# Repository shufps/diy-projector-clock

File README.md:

# DIY Night Projector Clock

A Clock Projector can project the time to a ceiling in the night.

There are lots of commercial alarm clocks with integrated clock projector on the market but I thought, it would be fun to build one myself.

Moreover it was a good project for becoming accustomed to the process of 3d-designing cases which can be 3d printed and to learn about designing tolerances.

The principle is easy – basically it works like a video beamer (or any other projecting clock^^).

## LCD and Calculations
I choosed a small negative (background black) 64×32 LCD which has the dimensions of just 15mm x 12mm (active area 11.18mm x 5.58mm).

The goal was to build a complete projector with not more than 50mm x 50mm x 50mm (which I didn’t managed … But close to^^).

A small LCD has the advantage that everything becomes smaller and cheaper – this influences heavily costs for optics because a smaller LCD needs smaller optics to project an low distorted image.

Moreover a smaller LCD needs smaller focal length for a decent sized imaged on the ceiling. A good distance would be 2m from LCD to ceiling.

The formula for image width depending from the focal length is defined as:

with:
– S2 distance from lens to LCD and
– S1 distance from lens to ceiling
– W2 is the width of the LCD
– W1 is the width of the projected image

The formulas show that the smaller the focal length the larger the projected image will be.

I decided to go for 25mm because there are cheap lenses which can be obtained for about $12 in china.

For our values that would magnify the image by about x80 – 11.1mm LCD width would become 88.1cm image width on the ceiling in a distance of 2m.

## Light and Condensor Lens
It was not really clear how strong a LED has to be in order to get a reasonable well readable picture in the night on the ceiling.

To be sure – actually I wasn’t really – I decided to use a high power LED with 1W and use a cheap chinese condensor lense to parallelize the light before it passes the LCD (this has do be done anyway but a condensor lens makes it possible to use more light because condensors are shaped in a way that allowes to get the lens as near to the LED as possible – so catching more light).

The two pictures show the condensor-lense which is directly mounted to the PCB the resulting light spot on the ceiling. It is a really gread lens which is made for my LED – so it fits perfectly and parallelizes the light nicely.

## Electronics Construction
Two PCBs were designed – one holding the LCD and the actual projecting board.

The latter is equipped with 1W LED driver, STM32F103 Cortex ARM, a rotary encoder (for changing settings like brightness, standby-timer, time, …), USB, IR (both not used yet).

## Mechanics Construction
Originally, I aimed for 50mm x 50mm x 50mm but I only managed to get to 60mm x 60mm x 60mm 😥 😉

Here an overview about all I designed:

From left to right: Case with DIY projection lens (I skip this part – it worked but not really well), Sony E-Mount, C-Mount. In the middle the rest.

## LCD-Holder
A custom LCD-holder was designed to perfectly mount the LCD on the right place on the PCB.

## Case – C-Mount Variant
There are incredibly cheap chinase C-Mount lenses with a focal length of 25mm. They are sooo cheap that image quality is really really bad when using for fotography.

But surprisingly it works (almost) perfect for the Mini DIY Projector 😀

The pillow-effect (optical distortion where the edges are not straight but bent outwards) is almost neglectable – resulting a much better image than I expected (after reading reviews to this lense)

## Case – Sony E-Mount Variant
Just for fun – and because I have a 3d printer which works reliably without much attention – I did a variant for Sony E-Mount.

Here the projector with Walimex Pro 10mm 2.8 lens.

I have to admit – it isn’t that bright in reality but it’s still very readable although it is so large.

The image has more than 2m in width! And distortions almost non-existent 🙂

Downloads
GitHub-Repository contains:
– Schematic
– Layout
– Bill of material
– STM32 Cortex ARM Source
– 3D-STL-Files
– Images

Thingiverse: https://www.thingiverse.com/thing:2887852

Archive of original site: https://web.archive.org/web/20241128173803/https://microengineer.eu/2018/05/01/diy-night-clock-projector/

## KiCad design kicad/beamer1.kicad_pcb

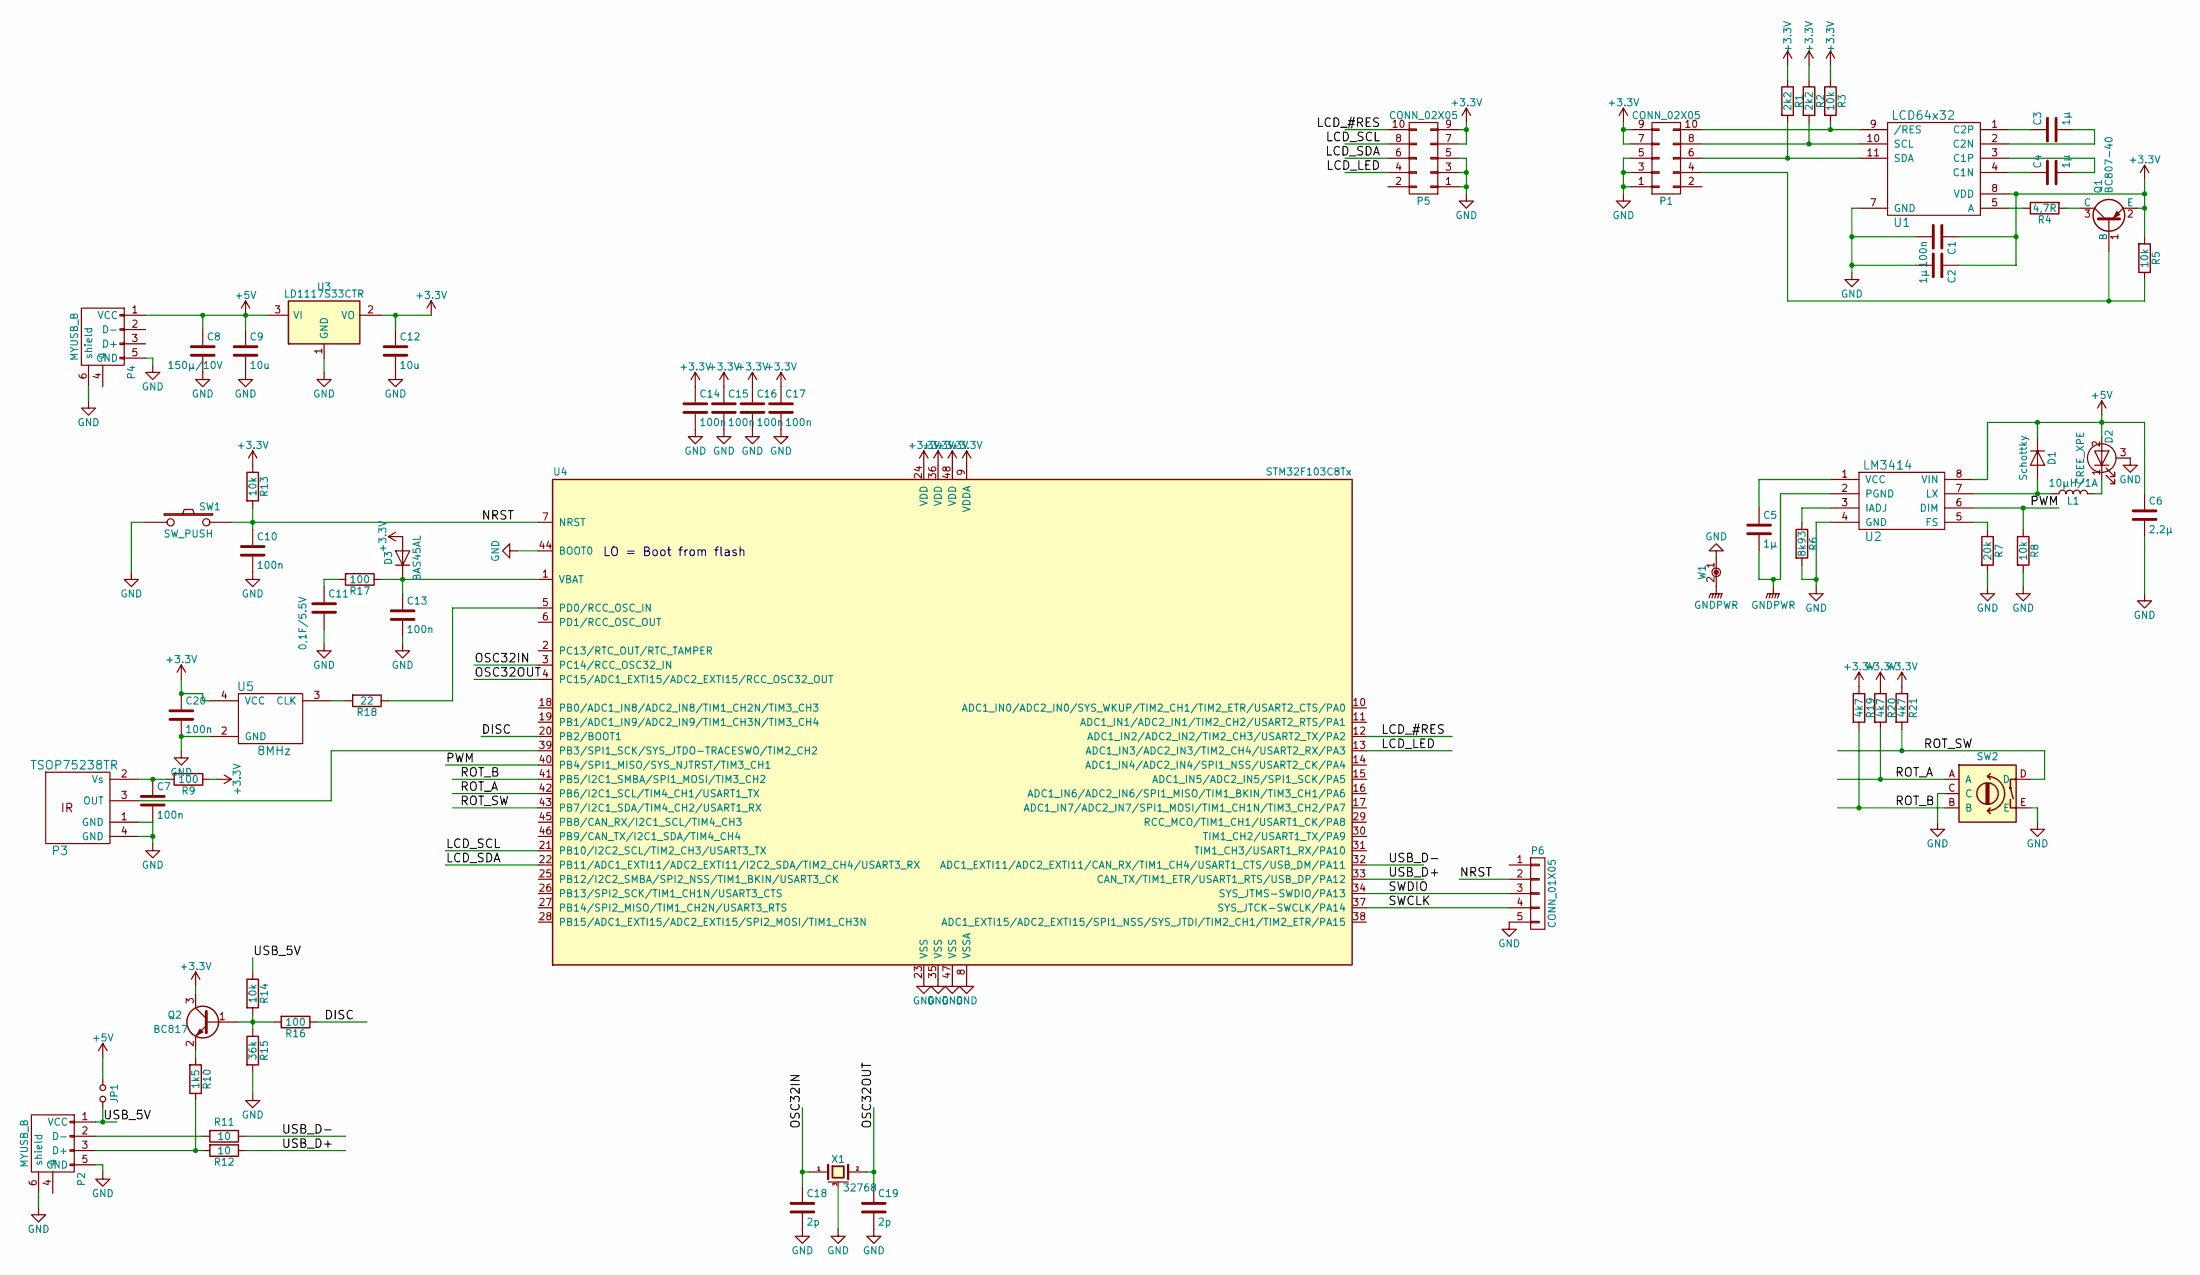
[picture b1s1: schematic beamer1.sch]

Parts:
C1: 100n; C_1206
C2, C3, C4, C5: 1µ; C_1206
C6: 2,2µ; C_1206
C7, C10, C13, C14, C15, C16, C17, C20: 100n; C_0805
C8: 150µ/10V; CP_Elec_8x6.7
C9, C12: 10u; C_1206
C11: 0,1F/5.5V; CP_Elec_10x7.7
C18, C19: 2p; C_0805
D1: Schottky; D_MiniMELF
D2: CREE_XPE; CREE_XLAMP_XP-E
D3: BAS45AL; D_0805
JP1: Jumper_NO_Small; SOLDERJMP
L1: 10µH/1A; Inductor_Taiyo-Yuden_NR-50xx
P1, P5: CONN_02X05; Pin_Header_Straight_2x05_Pitch2.54mm_SMD
P2, P4: MYUSB_B; MICROUSBB
P3: TSOP75238TR; TSOP752
P6: CONN_01X05; Pin_Header_Straight_1x05_Pitch1.27mm
Q1: BC807-40; SOT-23
Q2: BC817; SOT-23
R1, R2: 2k2; R_1206
R3, R5, R8: 10k; R_1206
R4: 4,7R; R_1210
R6: 8k93; R_1206
R7: 20k; R_1206
R9, R16, R17: 100; R_0805
R10: 1k5; R_0805
R11, R12: 10; R_0805
R13, R14: 10k; R_0805
R15: 36k; R_0805
R18: 22; R_0805
R19, R20, R21: 4k7; R_1206
SW1: SW_PUSH; KURZHUB_SMD
SW2: Rotary_Encoder_Switch_My; EC11B_ROTARY
U1: LCD64x32
U2: LM3414; SOIC-8-N
U3: LD1117S33CTR; SOT-223-3Lead_TabPin2
U4: STM32F103C8Tx; LQFP-48_7x7mm_Pitch0.5mm
U5: 8MHz; SMDOSZIL
W1: NET-TIE; NET-TIE-0.3mm
X1: 32768; Crystal_SMD_3215-2pin_3.2x1.5mm

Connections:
+3V3: C1.1, C2.1, C12.1, C14.1, C15.1, C16.1, C17.1, C20.1, D3.2 (A), P1.7, P1.9, P5.7, P5.9, Q1.2 (E), Q2.3 (C), R1.1, R2.1, R3.1, R5.2, R9.1, R13.1, R19.1, R20.1, R21.1, U1.8 (VDD), U3.2 (VO), U4.9 (VDDA), U4.24 (VDD), U4.36 (VDD), U4.48 (VDD), U5.4 (VCC)
+5V: C6.1, C8.1, C9.1, D1.1 (K), D2.2 (A), JP1.1, P4.1 (VCC), U2.8 (VIN), U3.3 (VI)
/DISC: R16.1, U4.20 (PB2/BOOT1)
/LCD_#RES: P5.10, U4.12 (ADC1_IN2/ADC2_IN2/TIM2_CH3/USART2_TX/PA2)
/LCD_LED: P5.4, U4.13 (ADC1_IN3/ADC2_IN3/TIM2_CH4/USART2_RX/PA3)
/LCD_SCL: P5.8, U4.21 (PB10/I2C2_SCL/TIM2_CH3/USART3_TX)
/LCD_SDA: P5.6, U4.22 (PB11/ADC1_EXTI11/ADC2_EXTI11/I2C2_SDA/T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)
/NRST: C10.1, P6.2, R13.2, SW1.2, U4.7 (NRST)
/OSC32IN: C18.1, U4.3 (PC14/RCC_OSC32_IN), X1.1
/OSC32OUT: C19.1, U4.4 (PC15/ADC1_EXTI15/ADC2_EXTI15/RCC_OSC32_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), X1.2
/PWM: R8.1, U2.6 (DIM), U4.40 (PB4/SPI1_MISO/SYS_NJTRST/TIM3_CH1)
/ROT_A: R20.2, SW2.A, U4.42 (PB6/I2C1_SCL/TIM4_CH1/USART1_TX)
/ROT_B: R19.2, SW2.B, U4.41 (PB5/I2C1_SMBA/SPI1_MOSI/TIM3_CH2)
/ROT_SW: R21.2, SW2.D, U4.43 (PB7/I2C1_SDA/TIM4_CH2/USART1_RX)
/SWCLK: P6.4, U4.37 (SYS_JTCK-SWCLK/PA14)
/SWDIO: P6.3, U4.34 (SYS_JTMS-SWDIO/PA13)
/USB_5V: JP1.2, P2.1 (VCC), R14.1
/USB_D+: R12.1, U4.33 (CAN_TX/TIM1_ETR/USART1_RTS/USB_DP/PA12)
/USB_D-: R11.1, U4.32 (ADC1_EXTI11/ADC2_EXTI11/CAN_RX/TIM1_CH4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)
GND: C1.2, C2.2, C6.2, C7.2, C8.2, C9.2, C10.2, C11.2, C12.2, C13.2, C14.2, C15.2, C16.2, C17.2, C18.2, C19.2, C20.2, D2.3 (TERM), P1.1, P1.3, P1.5, P2.5 (GND), P2.6 (shield), P3.1 (GND), P3.4 (GND), P4.5 (GND), P4.6 (shield), P5.1, P5.3, P5.5, P6.5, R6.2, R7.2, R8.2, R15.2, SW1.1, SW2.C, SW2.E, U1.7 (GND), U2.4 (GND), U3.1 (GND), U4.8 (VSSA), U4.23 (VSS), U4.35 (VSS), U4.44 (BOOT0), U4.47 (VSS), U5.2 (GND), W1.1, X1.3 (case)
GNDPWR: C5.2, U2.2 (PGND), W1.2
unnamed: C3.1, U1.1 (C2P)
unnamed: C3.2, U1.2 (C2N)
unnamed: C4.1, U1.4 (C1N)
unnamed: C4.2, U1.3 (C1P)
unnamed: C5.1, U2.1 (VCC)
unnamed: C7.1, P3.2 (Vs), R9.2
unnamed: C11.1, R17.2
unnamed: C13.1, D3.1 (K), R17.1, U4.1 (VBAT)
unnamed: D1.2 (A), L1.1, U2.7 (LX)
unnamed: D2.1 (K), L1.2
unnamed: P1.4, Q1.1 (B), R5.1
unnamed: P1.6, R1.2, U1.11 (SDA)
unnamed: P1.8, R2.2, U1.10 (SCL)
unnamed: P1.10, R3.2, U1.9 (/RES)
unnamed: P2.2 (D-), R11.2
unnamed: P2.3 (D+), R10.1, R12.2
unnamed: P3.3 (OUT), U4.39 (PB3/SPI1_SCK/SYS_JTDO-TRACESWO/TIM2_CH2)
unnamed: Q1.3 (C), R4.2
unnamed: Q2.1 (B), R14.2, R15.1, R16.2
unnamed: Q2.2 (E), R10.2
unnamed: R4.1, U1.5 (A)
unnamed: R6.1, U2.3 (IADJ)
unnamed: R7.1, U2.5 (FS)
unnamed: R18.1, U4.5 (PD0/RCC_OSC_IN)
unnamed: R18.2, U5.3 (CLK)

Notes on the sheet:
LO = Boot from flash

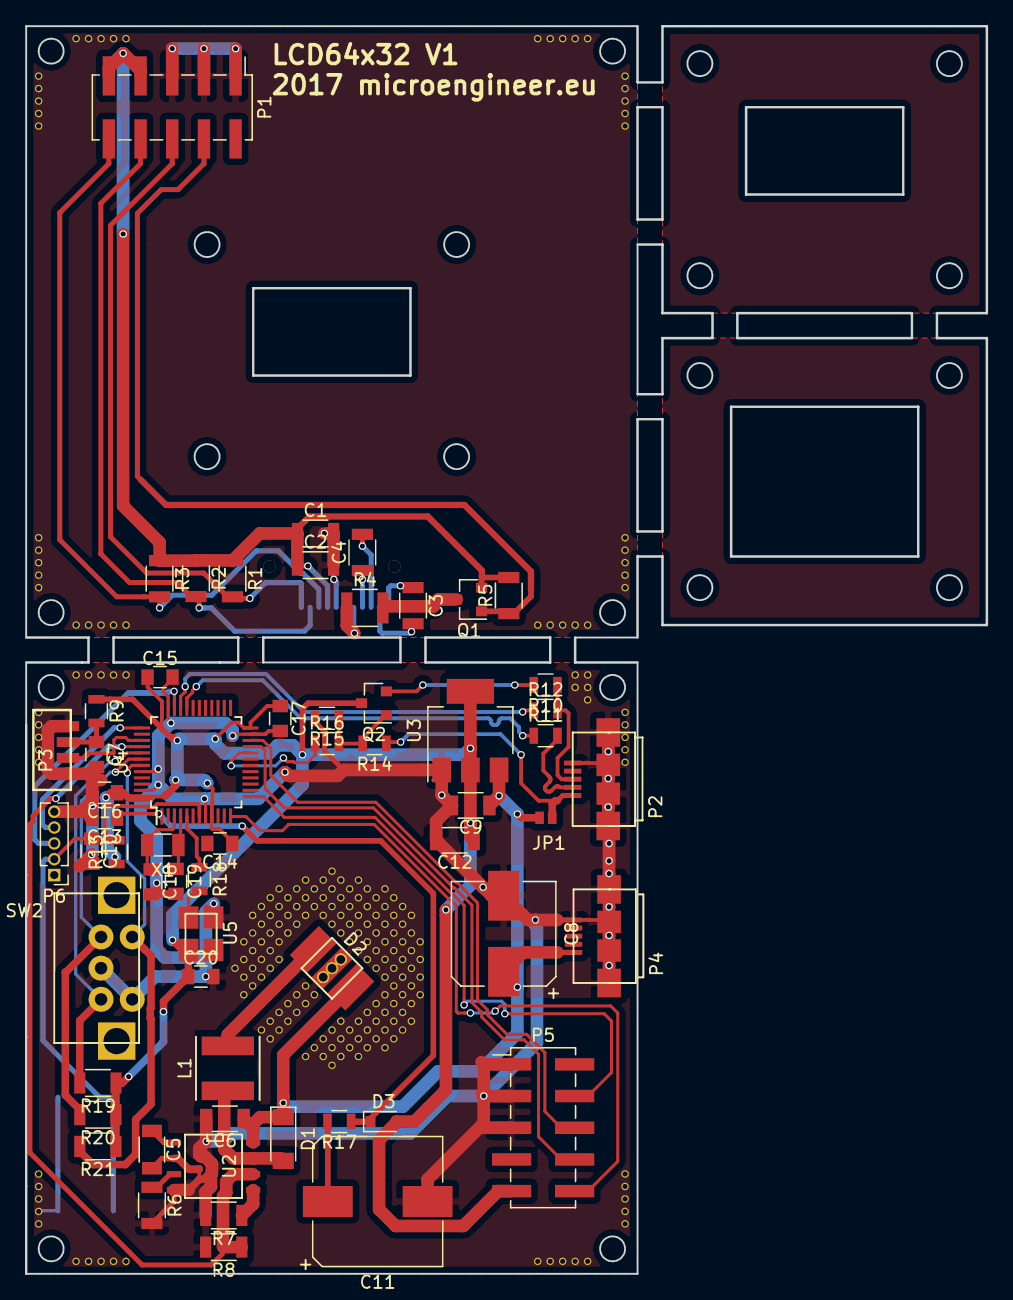
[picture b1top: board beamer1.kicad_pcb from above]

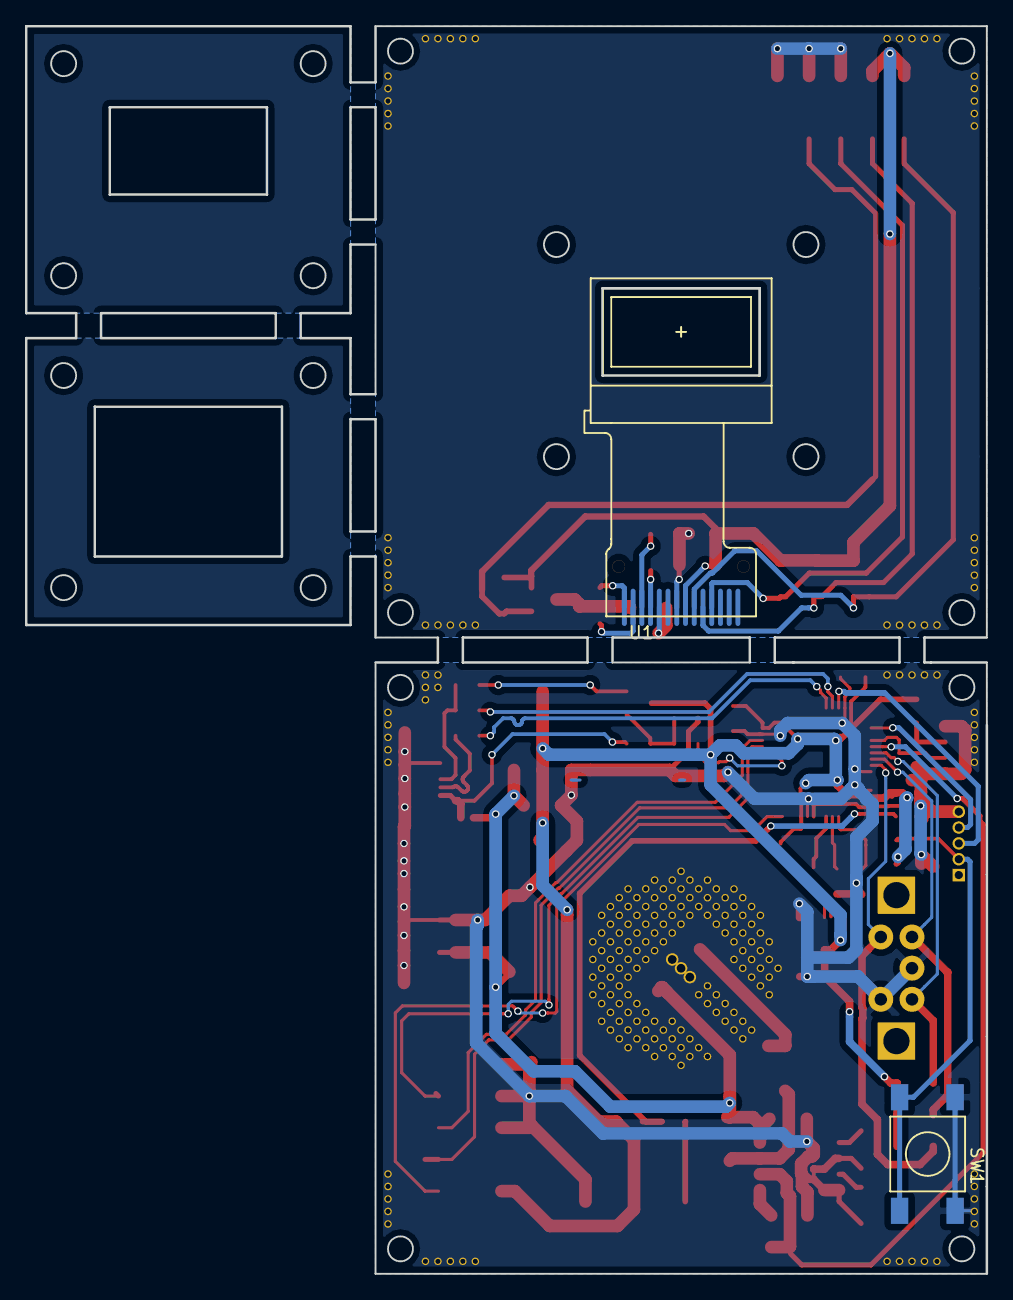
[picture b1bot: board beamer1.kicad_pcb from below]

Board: 2 copper layers, 77.0 x 100.0 mm, 63 parts (2 on the bottom side), 46 nets.

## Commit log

2018-05-05 gerber files for pcb
2019-12-18 trying to fix the 24hrs bug
2019-12-18 2nd fix for rtc_checkUpdateDate
2019-12-20 changed for alternative weekday names and tried to center the text
2020-11-13 added binary file
